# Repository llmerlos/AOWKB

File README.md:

# An Otter Keyboard

Personal project to develop a ergonomic split wireless/wired keyboard. Firmware for the wireless version can be found in [https://github.com/llmerlos/zmk-config-aokb]

## Keyboard specifications:
### Wireless:
* 2x PCB (reversible)
* 2x Switch Plate (reversible)
* 2x Seeed Studio XIAO NRF52840
* 2x MSK-12C02 switch
* 2x 51021 JST 1.25mm 2P Battery Connector
* 2x LiPo Battery 402535 3.7V 320mAh
* 40x IN4148W SOD-123 Diodes
* 40x Kail Choc Switches
* 40x Kail Choc Keycaps
* 40x Kail Chos Hotswap Sockets
* 12x M3 4mm Screws and Nuts

### Wired:
* 2x PCB (reversible)
* 2x Switch Plate (reversible)
* 2x Seeed Studio XIAO RP2040
* 2x TRRS-PJ-320A connector
* 40x IN4148W SOD-123 Diodes
* 40x Kail Choc Switches
* 40x Kail Choc Keycaps
* 40x Kail Chos Hotswap Sockets
* 12x M3 4mm Screws and Nuts

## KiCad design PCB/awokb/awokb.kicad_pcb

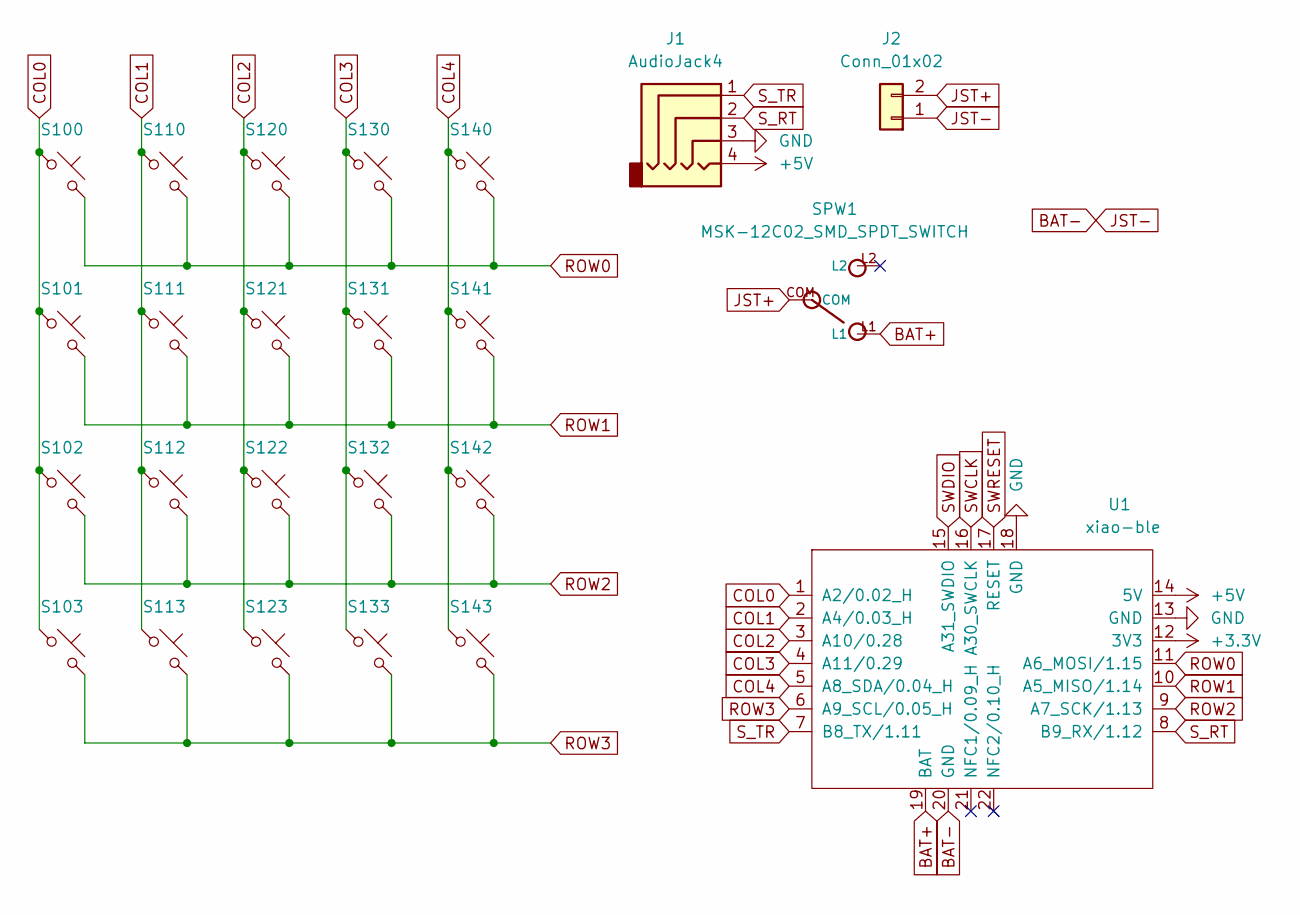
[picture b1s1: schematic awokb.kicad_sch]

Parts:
J1: AudioJack4; TRRS-PJ-320A_Mirr
J2: Conn_01x02; JST_PH_B2B-PH-K_1x02_P2.00mm_Vertical
S100, S101, S102, S103, S110, S111, S112, S113, S120, S121, S122, S123, S130, S131, S132, S133, S140, S141, S142, S143: SW_Push_45deg; Choc_HS_R_SOD
SPW1: MSK-12C02_SMD_SPDT_SWITCH; MSK-12C02
U1: xiao-ble; xiao-ble-smd_r

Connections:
+3V3: U1.12 (3V3)
+5V: J1.4, U1.14 (5V)
BAT+: SPW1.L1, U1.19 (BAT)
BAT-: J2.1, U1.20 (GND)
COL0: S100.1, S101.1, S102.1, S103.1, U1.1 (A2/0.02_H)
COL1: S110.1, S111.1, S112.1, S113.1, U1.2 (A4/0.03_H)
COL2: S120.1, S121.1, S122.1, S123.1, U1.3 (A10/0.28)
COL3: S130.1, S131.1, S132.1, S133.1, U1.4 (A11/0.29)
COL4: S140.1, S141.1, S142.1, S143.1, U1.5 (A8_SDA/0.04_H)
GND: J1.3, U1.13 (GND), U1.18 (GND)
JST+: J2.2, SPW1.COM
ROW0: S100.2, S110.2, S120.2, S130.2, S140.2, U1.11 (A6_MOSI/1.15)
ROW1: S101.2, S111.2, S121.2, S131.2, S141.2, U1.10 (A5_MISO/1.14)
ROW2: S102.2, S112.2, S122.2, S132.2, S142.2, U1.9 (A7_SCK/1.13)
ROW3: S103.2, S113.2, S123.2, S133.2, S143.2, U1.6 (A9_SCL/0.05_H)
SWCLK: U1.16 (A30_SWCLK)
SWDIO: U1.15 (A31_SWDIO)
SWRESET: U1.17 (RESET)
S_RT: J1.2, U1.8 (B9_RX/1.12)
S_TR: J1.1, U1.7 (B8_TX/1.11)

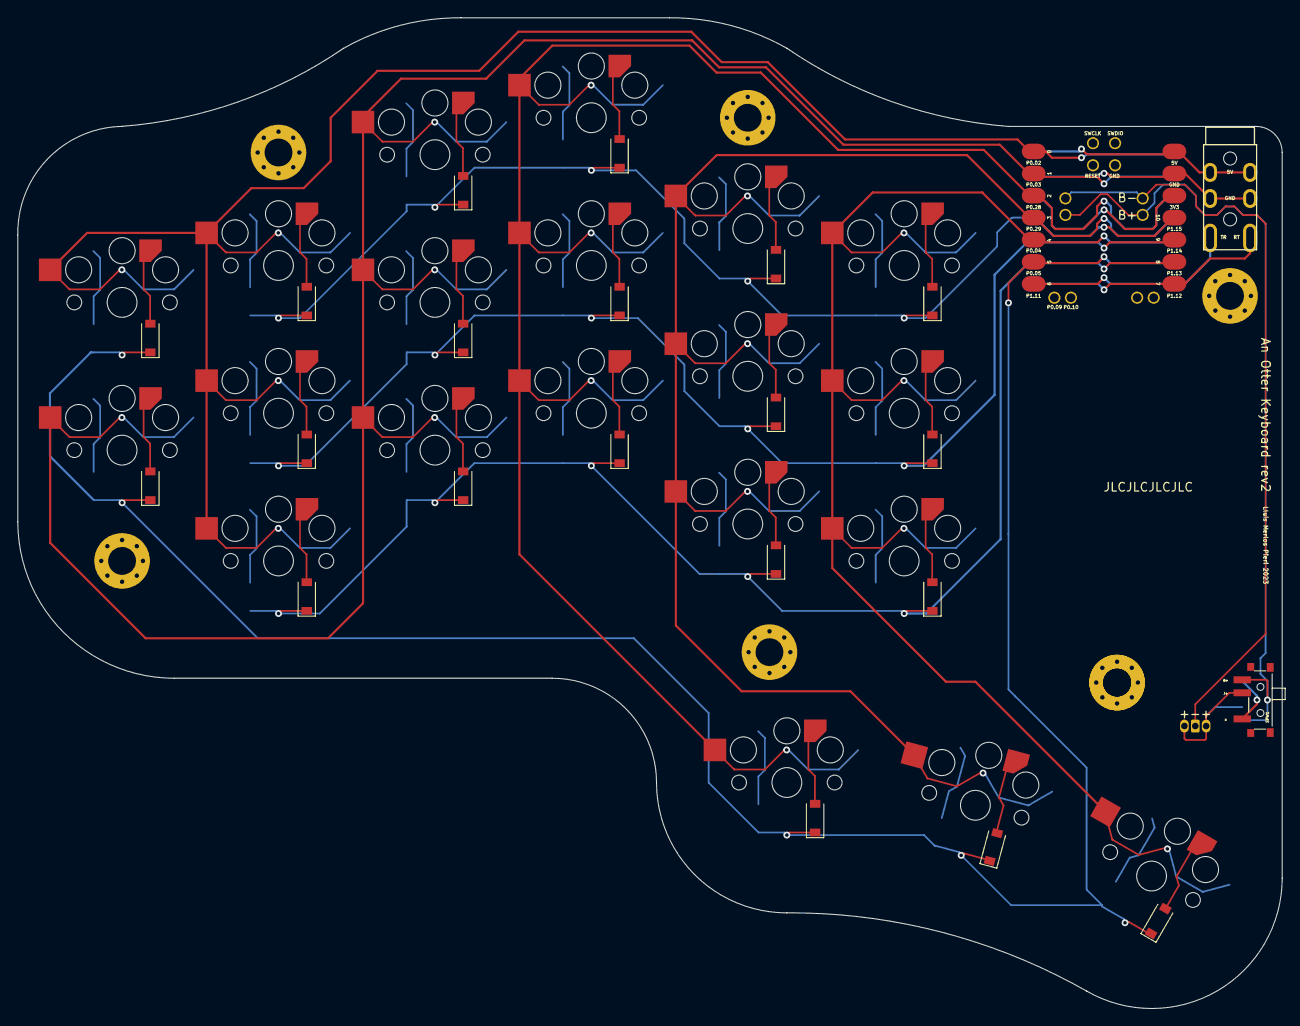
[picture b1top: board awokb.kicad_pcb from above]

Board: 2 copper layers, 145.5 x 114.0 mm, 24 parts (0 on the bottom side), 16 nets.

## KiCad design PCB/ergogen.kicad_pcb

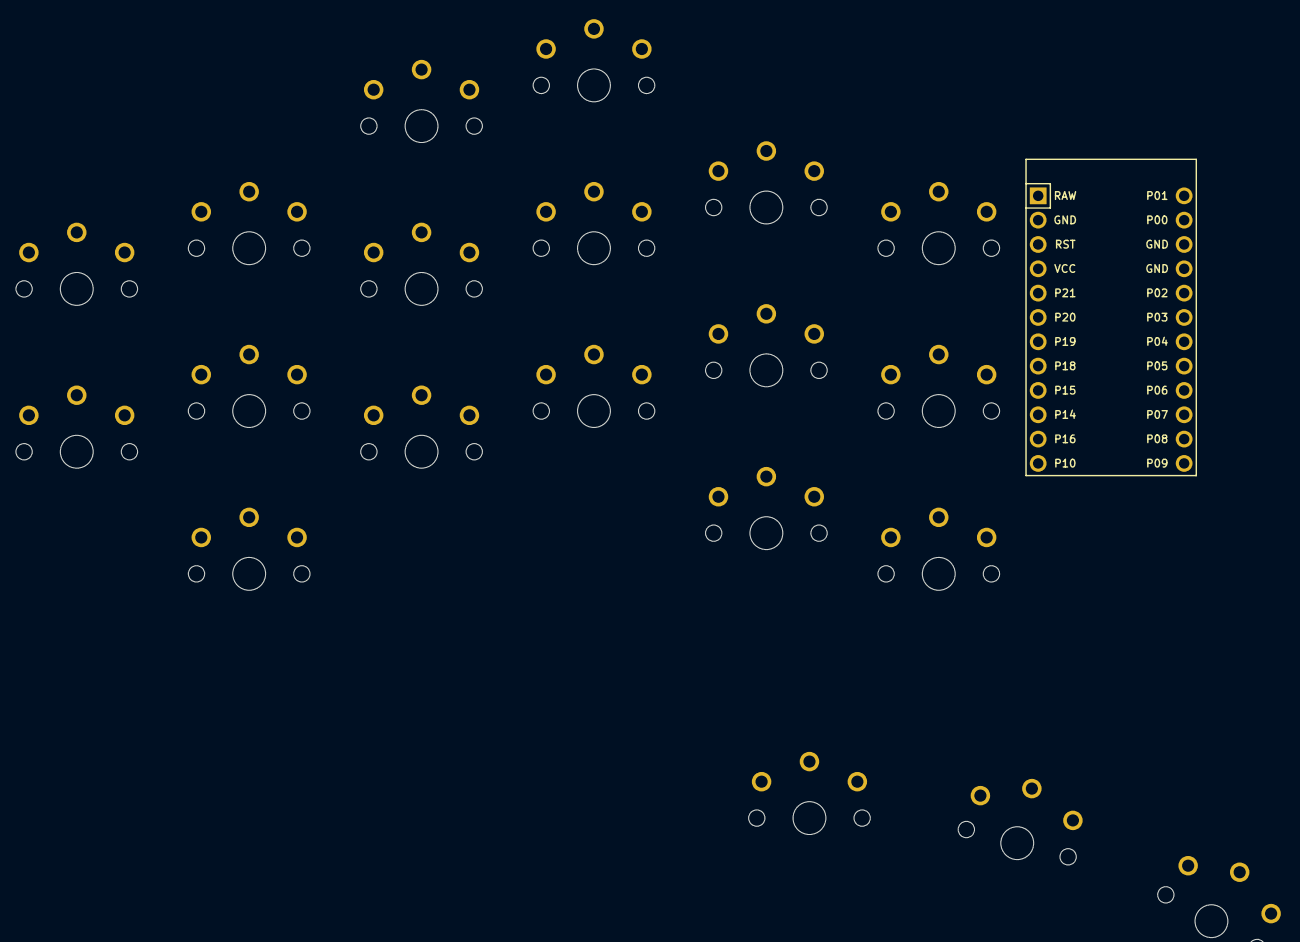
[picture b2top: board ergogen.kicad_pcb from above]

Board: 2 copper layers, 21 parts (0 on the bottom side), 18 nets, no tracks yet.

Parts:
MCU1: ProMicro
S1, S2, S3, S4, S5, S6, S7, S8, S9, S10, S11, S12, S13, S14, S15, S16, S17, S18, S19, S20: PG1350

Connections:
GND: MCU1.2, MCU1.15, MCU1.16, S1.1, S2.1, S3.1, S4.1, S5.1, S6.1, S7.1, S8.1, S9.1, S10.1, S11.1, S12.1, S13.1, S14.1, S15.1, S16.1, S17.1, S18.1, S19.1, S20.1
matrix_index_bottom: MCU1.20, S10.2
matrix_index_home: MCU1.12, S11.2
matrix_index_top: MCU1.6, S12.2
matrix_inner_bottom: MCU1.21, S13.2
matrix_inner_home: MCU1.13, S14.2
matrix_inner_top: MCU1.5, S15.2
matrix_middle_bottom: MCU1.19, S7.2
matrix_middle_home: MCU1.11, S8.2
matrix_middle_top: MCU1.7, S9.2
matrix_pinky_bottom: MCU1.17, S1.2
matrix_pinky_home: MCU1.9, S2.2
matrix_pinky_top: MCU1.22, S3.2
matrix_ring_bottom: MCU1.18, S4.2
matrix_ring_home: MCU1.10, S5.2
matrix_ring_top: MCU1.8, S6.2
thumb_reachy: MCU1.24, S19.2
thumb_tucky: MCU1.23, S18.2
